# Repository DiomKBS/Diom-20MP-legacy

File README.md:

# Diom-20MP
Macro Pad for all the cool bois

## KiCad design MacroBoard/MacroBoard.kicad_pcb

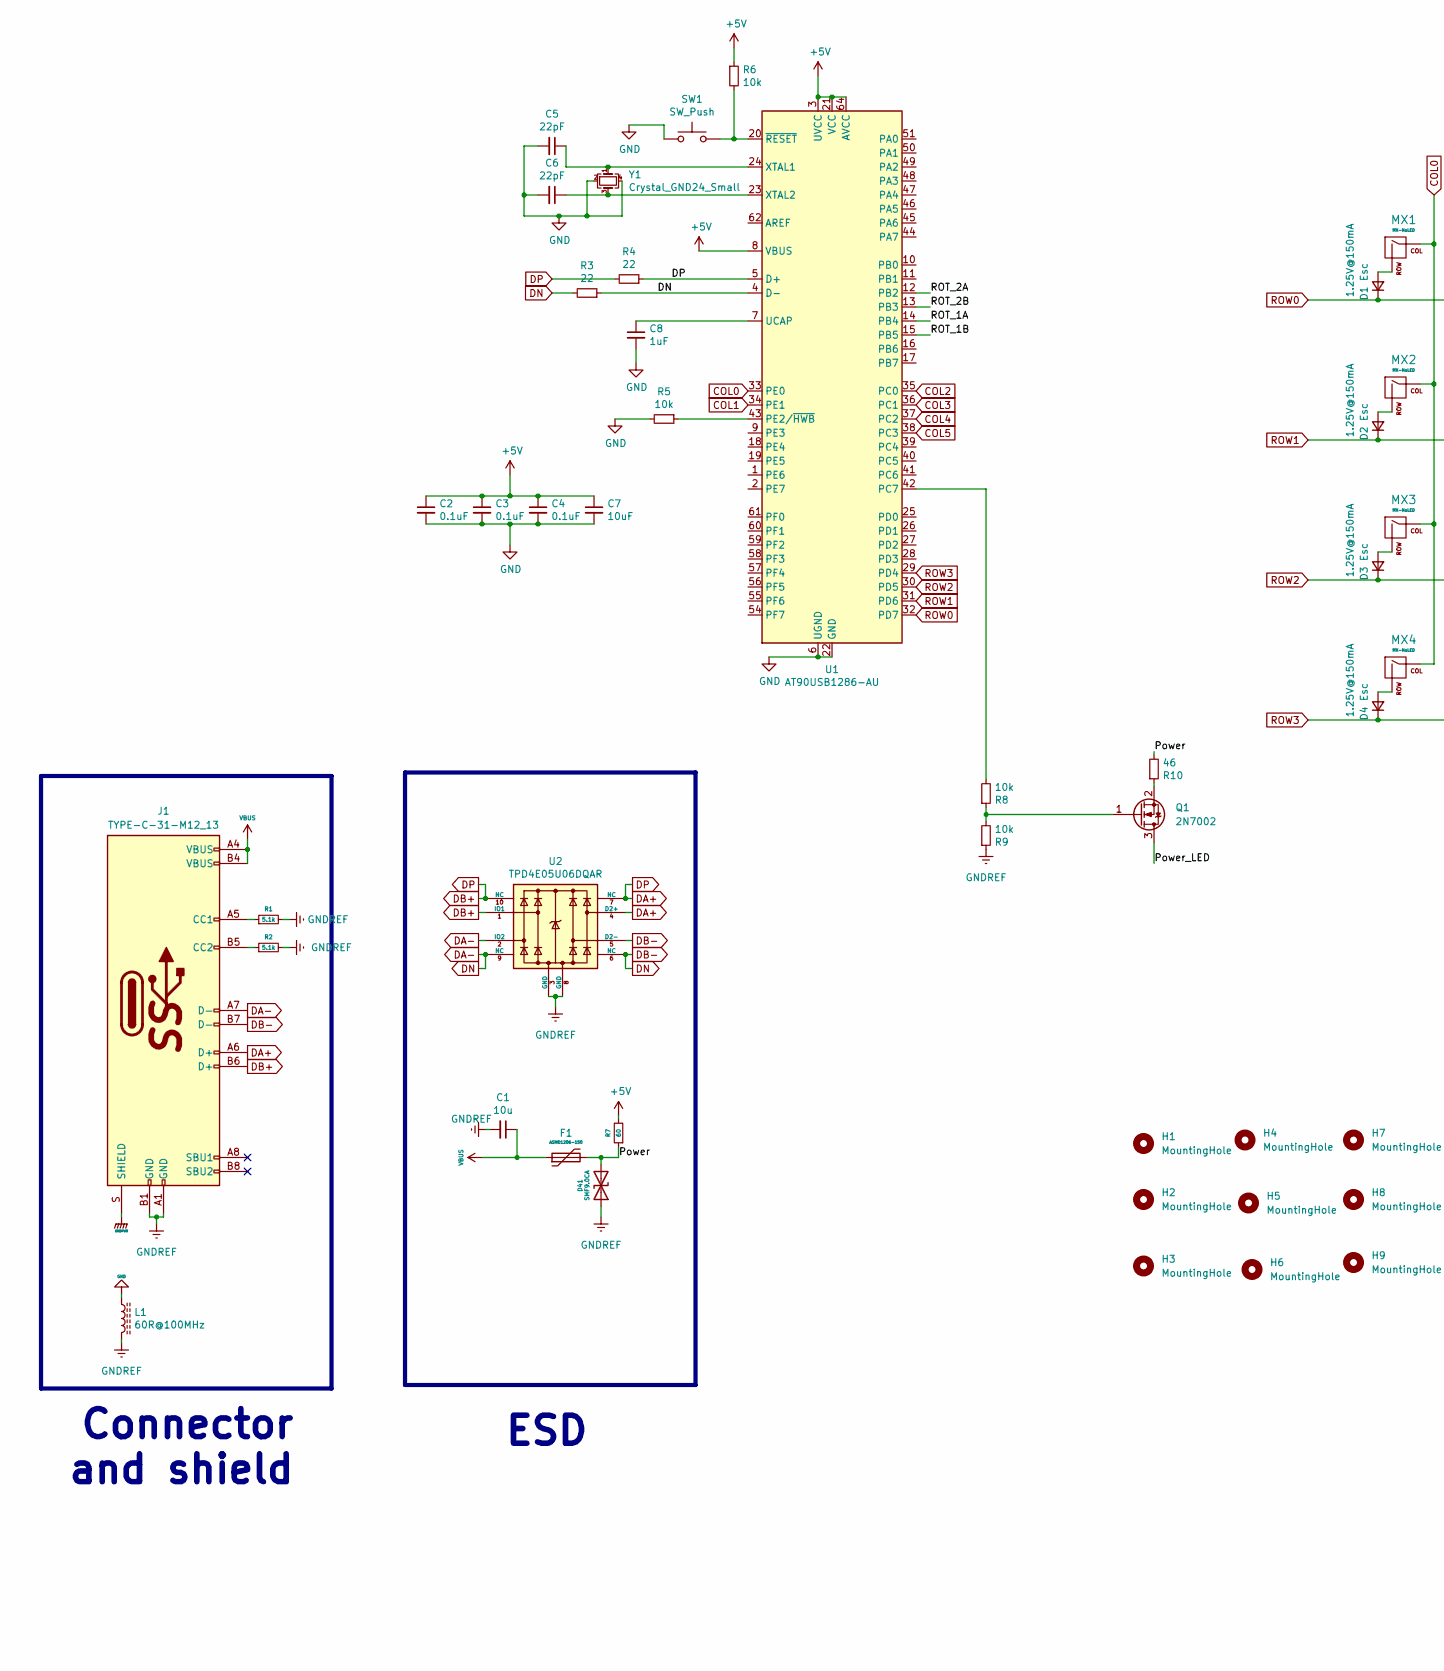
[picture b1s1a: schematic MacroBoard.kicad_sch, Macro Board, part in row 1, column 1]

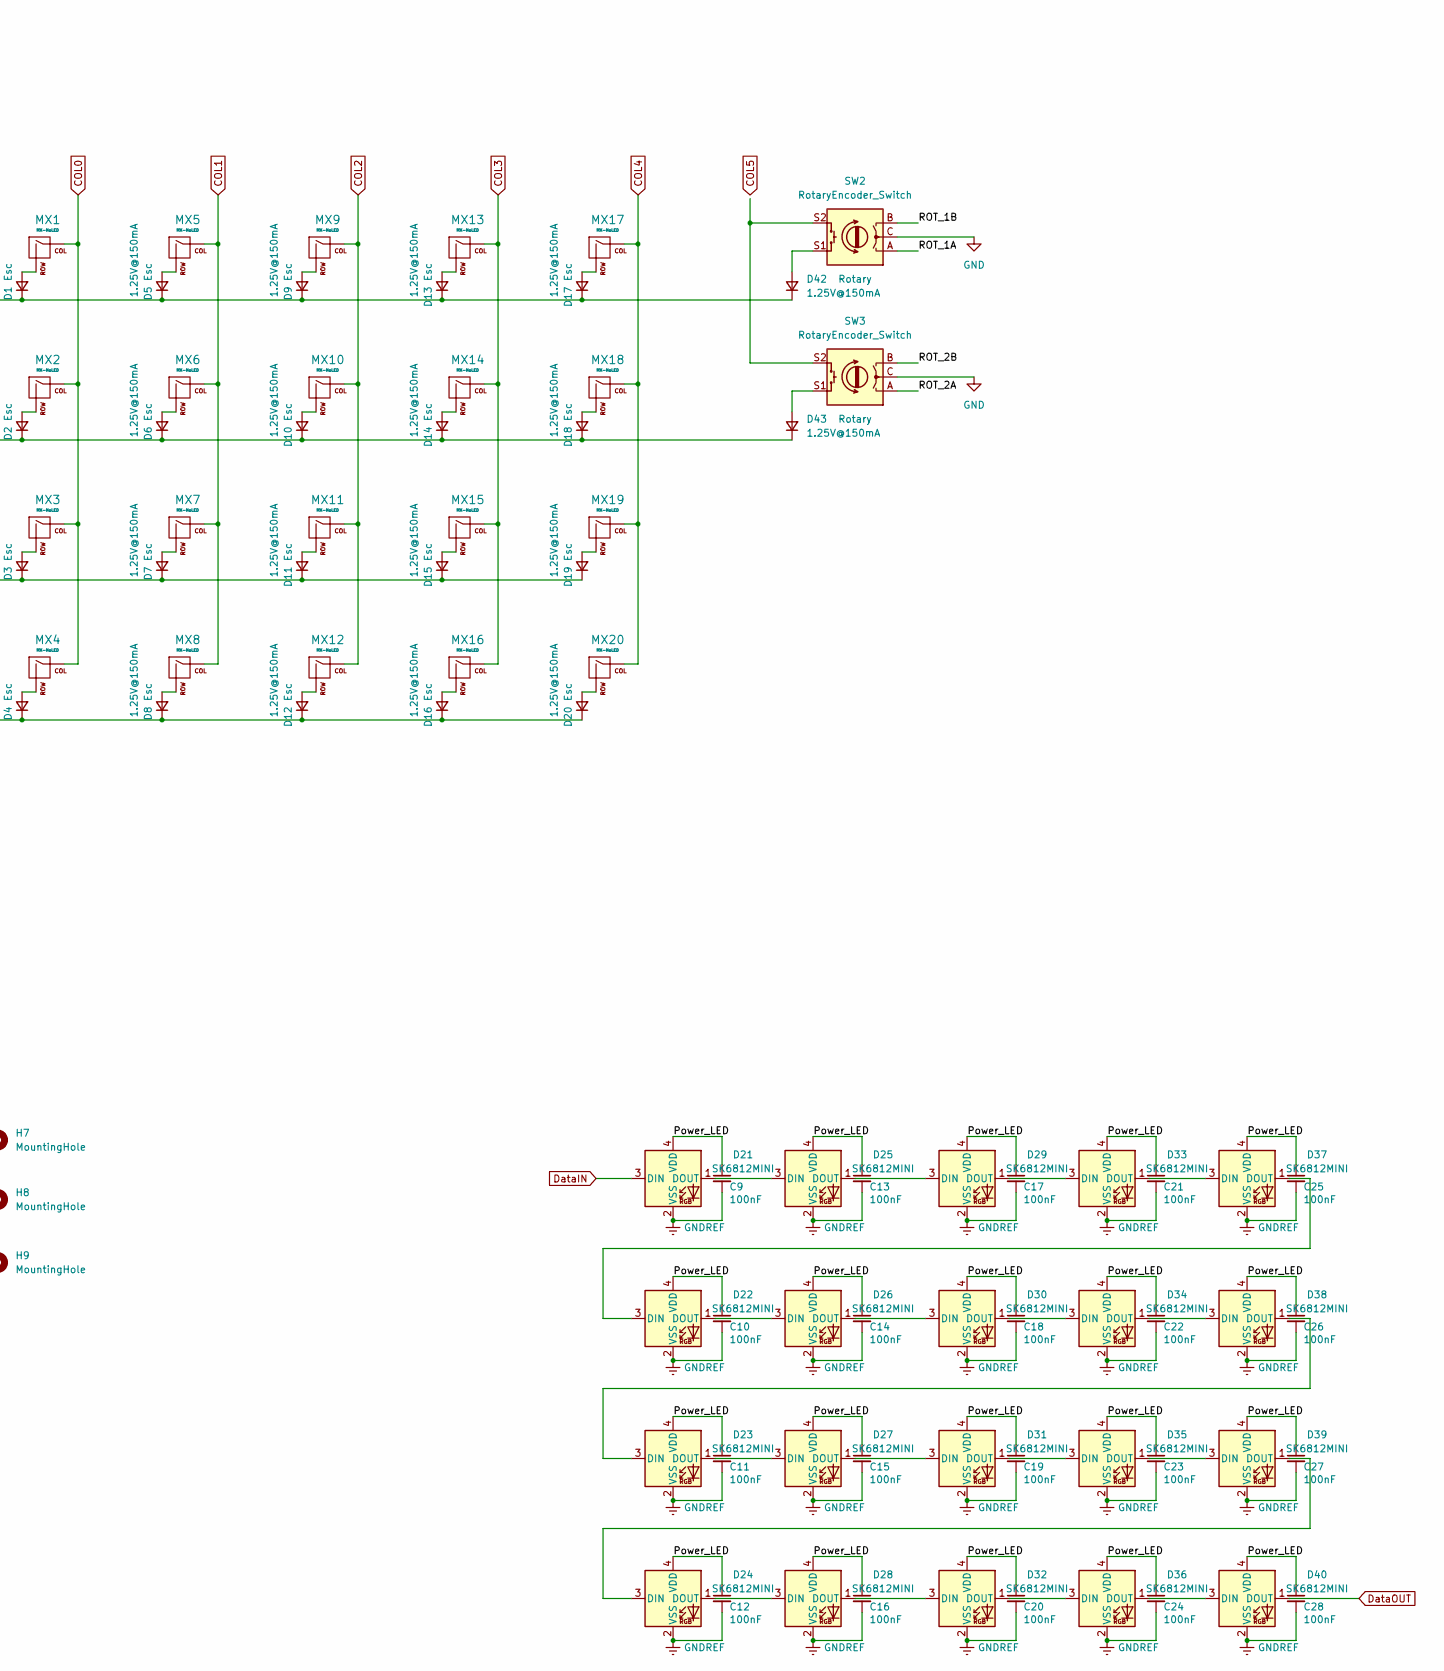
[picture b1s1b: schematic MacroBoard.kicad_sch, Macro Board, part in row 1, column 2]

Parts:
C1: 10u; C_0805_2012Metric
C2, C3, C4: 0.1uF; C_0805_2012Metric
C5, C6: 22pF; C_0805_2012Metric
C7: 10uF; C_0805_2012Metric
C8: 1uF; C_0805_2012Metric
C9, C10, C11, C12, C13, C14, C15, C16, C17, C18, C19, C20, C21, C22, C23, C24, C25, C26, C27, C28: 100nF; led_capacitor
D1, D2, D3, D4, D5, D6, D7, D8, D9, D10, D11, D12, D13, D14, D15, D16, D17, D18, D19, D20, D42, D43: 1.25V@150mA; D_SOD-123
D21, D22, D23, D24, D25, D26, D27, D28, D29, D30, D31, D32, D33, D34, D35, D36, D37, D38, D39, D40: SK6812MINI; SK6812MINI_3.5x3.7mm_SMD-Flipped-Back
D41: SMF9.0CA; D_SOD-123; Manufacturer Part No SMF9.0CA; LCSC Part No C123799
F1: ASMD1206-150; Fuse_0603_1608Metric_Pad1.05x0.95mm_HandSolder; Manufacturer Part No ASMD1206-150; LCSC Part No C135342
H1, H2, H3, H4, H5, H6, H7, H8, H9: MountingHole; MountingHole_2.2mm_M2
J1: TYPE-C-31-M12_13; TYPE-C-31-M-12; Manufacturer Part No TYPE-C-31-M-12; LCSC Part No C165948
L1: 60R@100MHz; L_1206_3216Metric; Manufacturer Part No MLB3216-600P4A(f); LCSC Part No C33600
MX1, MX2, MX3, MX4, MX5, MX6, MX7, MX8, MX9, MX10, MX11, MX12, MX13, MX14, MX15, MX16, MX17, MX18, MX19, MX20: MX-NoLED; Kailh-Hotswap-1U
Q1: 2N7002; SOT-23; LCSC Part C916396
R1, R2: 5.1k; R_0402_1005Metric_Pad0.72x0.64mm_HandSolder
R3, R4: 22; R_0805_2012Metric
R5, R6: 10k; R_0805_2012Metric
R7: 60; R_0805_2012Metric_Pad1.20x1.40mm_HandSolder
R8, R9: 10k; R_0805_2012Metric; LCSC Part C2907219
R10: 46; R_0805_2012Metric; LCSC Part C2907219
SW1: SW_Push; switch_without_switch
SW2, SW3: RotaryEncoder_Switch; RotaryEncoder_EC11E-Switch
U1: AT90USB1286-AU; TQFP-64_14x14mm_P0.8mm
U2: TPD4E05U06DQAR; USON-10_2.5x1.0mm_P0.5mm; Manufacturer Part No TPD4E05U06DQAR; LCSC Part No C138714
Y1: Crystal_GND24_Small; Crystal_SMD_3225-4Pin_3.2x2.5mm

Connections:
+5V: C2.1, C3.1, C4.1, C7.1, R6.1, R7.2, U1.3 (UVCC), U1.8 (VBUS), U1.21 (VCC), U1.52 (VCC), U1.64 (AVCC)
/Power: D41.2 (A2), F1.2, R7.1, R10.2
/Power_LED: C9.1, C10.1, C11.1, C12.1, C13.1, C14.1, C15.1, C16.1, C17.1, C18.1, C19.1, C20.1, C21.1, C22.1, C23.1, C24.1, C25.1, C26.1, C27.1, C28.1, D21.4 (VDD), D22.4 (VDD), D23.4 (VDD), D24.4 (VDD), D25.4 (VDD), D26.4 (VDD), D27.4 (VDD), D28.4 (VDD), D29.4 (VDD), D30.4 (VDD), D31.4 (VDD), D32.4 (VDD), D33.4 (VDD), D34.4 (VDD), D35.4 (VDD), D36.4 (VDD), D37.4 (VDD), D38.4 (VDD), D39.4 (VDD), D40.4 (VDD), Q1.3 (D)
/ROT_1A: SW2.A, U1.14 (PB4)
/ROT_1B: SW2.B, U1.15 (PB5)
/ROT_2A: SW3.A, U1.12 (PB2)
/ROT_2B: SW3.B, U1.13 (PB3)
COL0: MX1.1 (COL), MX2.1 (COL), MX3.1 (COL), MX4.1 (COL), U1.33 (PE0)
COL1: MX5.1 (COL), MX6.1 (COL), MX7.1 (COL), MX8.1 (COL), U1.34 (PE1)
COL2: MX9.1 (COL), MX10.1 (COL), MX11.1 (COL), MX12.1 (COL), U1.35 (PC0)
COL3: MX13.1 (COL), MX14.1 (COL), MX15.1 (COL), MX16.1 (COL), U1.36 (PC1)
COL4: MX17.1 (COL), MX18.1 (COL), MX19.1 (COL), MX20.1 (COL), U1.37 (PC2)
COL5: U1.38 (PC3)
DA+: J1.A6 (D+), J1.B6 (D+), R4.1, R4.2, U1.5 (D+), U2.1 (IO1), U2.4 (D2+), U2.7 (NC), U2.10 (NC)
DA-: J1.A7 (D-), J1.B7 (D-), R3.1, R3.2, U1.4 (D-), U2.2 (IO2), U2.5 (D2-), U2.6 (NC), U2.9 (NC)
DataIN: D21.3 (DIN)
DataOUT: D40.1 (DOUT)
GND: C2.2, C3.2, C4.2, C5.2, C6.2, C7.2, C8.2, L1.1, R5.2, SW1.1, SW2.C, SW3.C, U1.6 (UGND), U1.22 (GND), U1.53 (GND), U1.63 (GND), Y1.2, Y1.4
GNDPWR: J1.S (SHIELD)
GNDREF: C1.2, C9.2, C10.2, C11.2, C12.2, C13.2, C14.2, C15.2, C16.2, C17.2, C18.2, C19.2, C20.2, C21.2, C22.2, C23.2, C24.2, C25.2, C26.2, C27.2, C28.2, D21.2 (VSS), D22.2 (VSS), D23.2 (VSS), D24.2 (VSS), D25.2 (VSS), D26.2 (VSS), D27.2 (VSS), D28.2 (VSS), D29.2 (VSS), D30.2 (VSS), D31.2 (VSS), D32.2 (VSS), D33.2 (VSS), D34.2 (VSS), D35.2 (VSS), D36.2 (VSS), D37.2 (VSS), D38.2 (VSS), D39.2 (VSS), D40.2 (VSS), D41.1 (A1), J1.A1 (GND), J1.B1 (GND), L1.2, R1.2, R2.2, R9.1, U2.3 (GND), U2.8 (GND)
unnamed: C5.1, U1.24 (XTAL1), Y1.1
unnamed: C6.1, U1.23 (XTAL2), Y1.3
unnamed: C8.1, U1.7 (UCAP)
unnamed: D1.2 (A), MX1.2 (ROW)
unnamed: D2.2 (A), MX2.2 (ROW)
unnamed: D3.2 (A), MX3.2 (ROW)
unnamed: D4.2 (A), MX4.2 (ROW)
unnamed: D5.2 (A), MX5.2 (ROW)
unnamed: D6.2 (A), MX6.2 (ROW)
unnamed: D7.2 (A), MX7.2 (ROW)
unnamed: D8.2 (A), MX8.2 (ROW)
unnamed: D9.2 (A), MX9.2 (ROW)
unnamed: D10.2 (A), MX10.2 (ROW)
unnamed: D11.2 (A), MX11.2 (ROW)
unnamed: D12.2 (A), MX12.2 (ROW)
unnamed: D13.2 (A), MX13.2 (ROW)
unnamed: D14.2 (A), MX14.2 (ROW)
unnamed: D15.2 (A), MX15.2 (ROW)
unnamed: D16.2 (A), MX16.2 (ROW)
unnamed: D17.2 (A), MX17.2 (ROW)
unnamed: D18.2 (A), MX18.2 (ROW)
unnamed: D19.2 (A), MX19.2 (ROW)
unnamed: D20.2 (A), MX20.2 (ROW)
unnamed: D21.1 (DOUT), D25.3 (DIN)
unnamed: D22.1 (DOUT), D26.3 (DIN)
unnamed: D22.3 (DIN), D37.1 (DOUT)
unnamed: D23.1 (DOUT), D27.3 (DIN)
unnamed: D23.3 (DIN), D38.1 (DOUT)
unnamed: D24.1 (DOUT), D28.3 (DIN)
unnamed: D24.3 (DIN), D39.1 (DOUT)
unnamed: D25.1 (DOUT), D29.3 (DIN)
unnamed: D26.1 (DOUT), D30.3 (DIN)
unnamed: D27.1 (DOUT), D31.3 (DIN)
unnamed: D28.1 (DOUT), D32.3 (DIN)
unnamed: D29.1 (DOUT), D33.3 (DIN)
unnamed: D30.1 (DOUT), D34.3 (DIN)
unnamed: D31.1 (DOUT), D35.3 (DIN)
unnamed: D32.1 (DOUT), D36.3 (DIN)
unnamed: D33.1 (DOUT), D37.3 (DIN)
unnamed: D34.1 (DOUT), D38.3 (DIN)
unnamed: D35.1 (DOUT), D39.3 (DIN)
unnamed: D36.1 (DOUT), D40.3 (DIN)
unnamed: D42.2 (A), SW2.S1
unnamed: D43.2 (A), SW3.S1
unnamed: J1.A5 (CC1), R1.1
unnamed: J1.B5 (CC2), R2.1
unnamed: Q1.1 (G), R8.1, R9.2
unnamed: Q1.2 (S), R10.1
unnamed: R5.1, U1.43 (PE2/~HWB)
unnamed: R6.2, SW1.2, U1.20 (~RESET)
unnamed: SW2.S2, SW3.S2
unnamed: R8.2, U1.42 (PC7)
ROW0: D1.1 (K), D5.1 (K), D9.1 (K), D13.1 (K), D17.1 (K), D42.1 (K), U1.32 (PD7)
ROW1: D2.1 (K), D6.1 (K), D10.1 (K), D14.1 (K), D18.1 (K), D43.1 (K), U1.31 (PD6)
ROW2: D3.1 (K), D7.1 (K), D11.1 (K), D15.1 (K), D19.1 (K), U1.30 (PD5)
ROW3: D4.1 (K), D8.1 (K), D12.1 (K), D16.1 (K), D20.1 (K), U1.29 (PD4)
VBUS: C1.1, F1.1, J1.A4 (VBUS), J1.B4 (VBUS)

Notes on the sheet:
Connector and shield
ESD

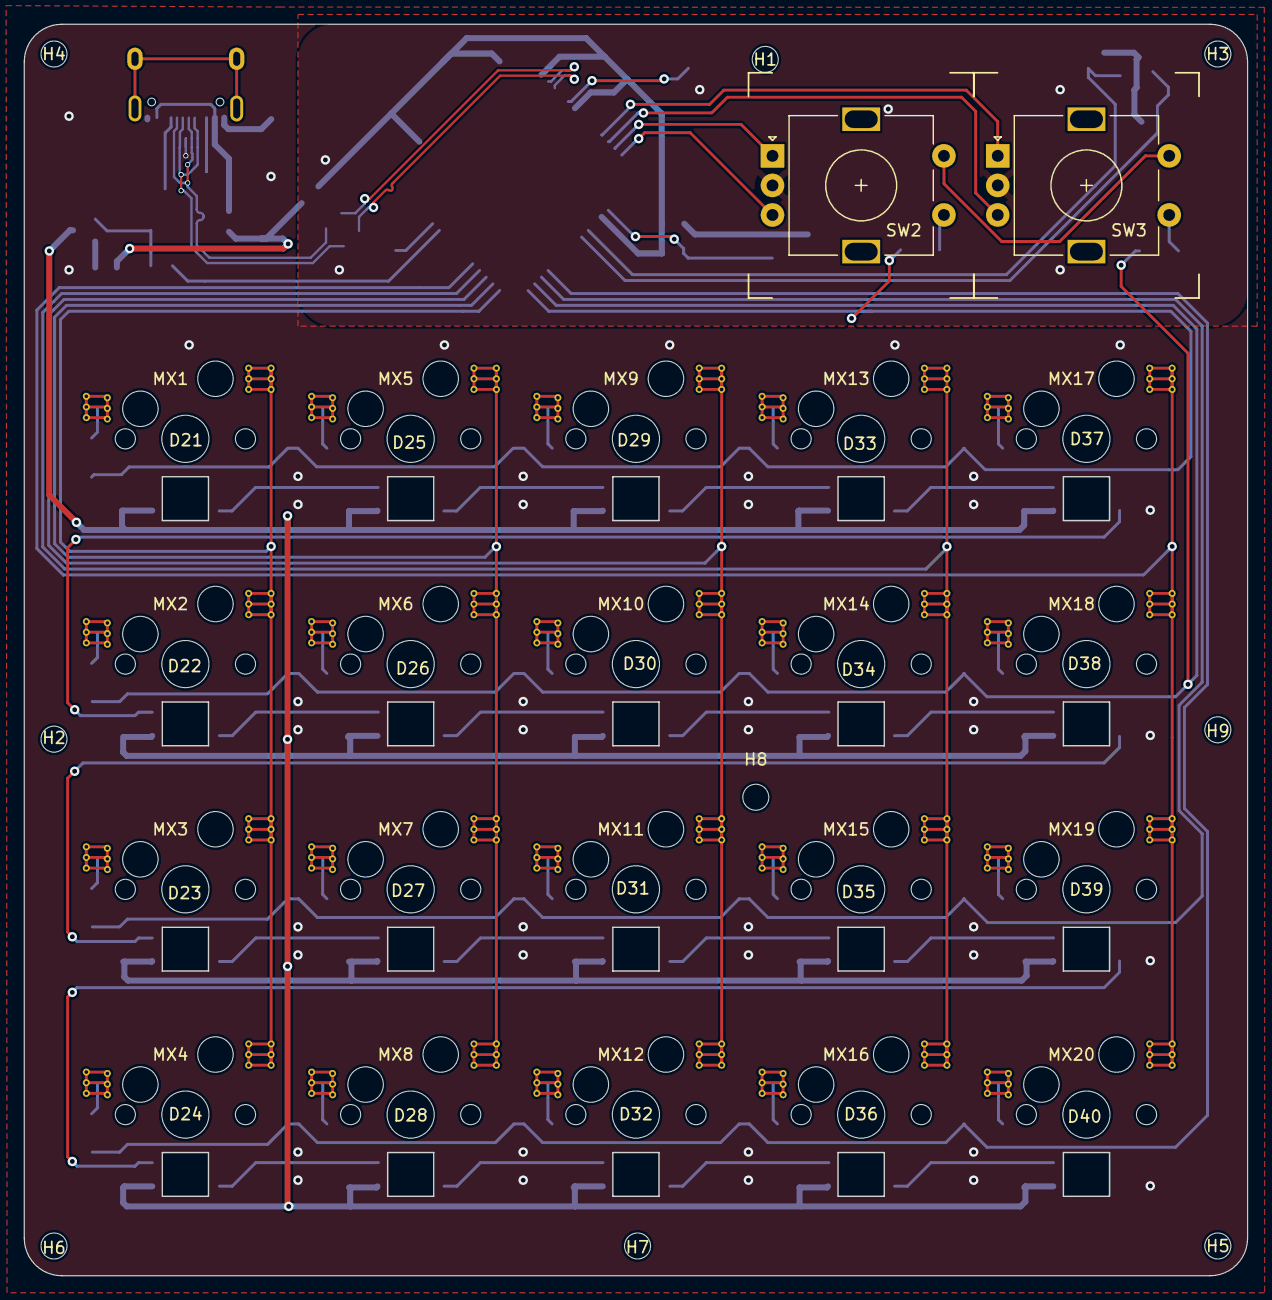
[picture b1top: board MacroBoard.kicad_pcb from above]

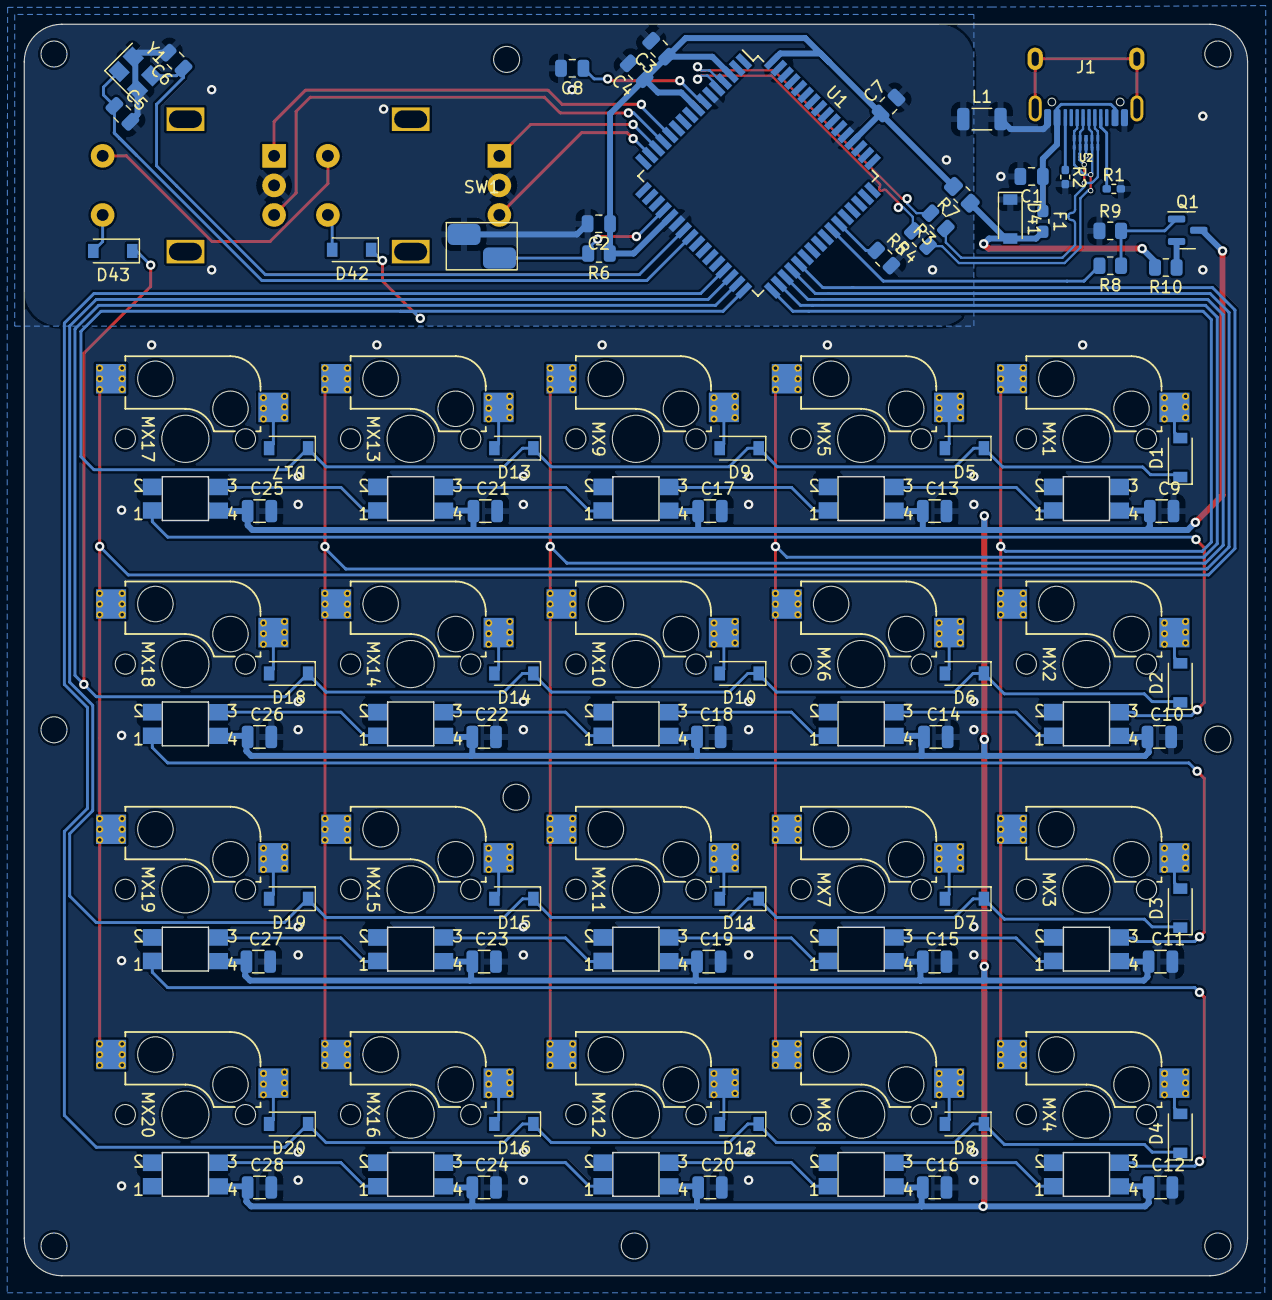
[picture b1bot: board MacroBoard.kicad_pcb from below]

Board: 2 copper layers, 103.4 x 105.8 mm, 120 parts (69 on the bottom side), 73 nets.

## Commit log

2022-04-24 init
2022-05-12 finished
2022-05-24 cleanup
2022-06-19 minor changes
2022-06-27 generate final Gerber
2022-11-01 fixed lights
